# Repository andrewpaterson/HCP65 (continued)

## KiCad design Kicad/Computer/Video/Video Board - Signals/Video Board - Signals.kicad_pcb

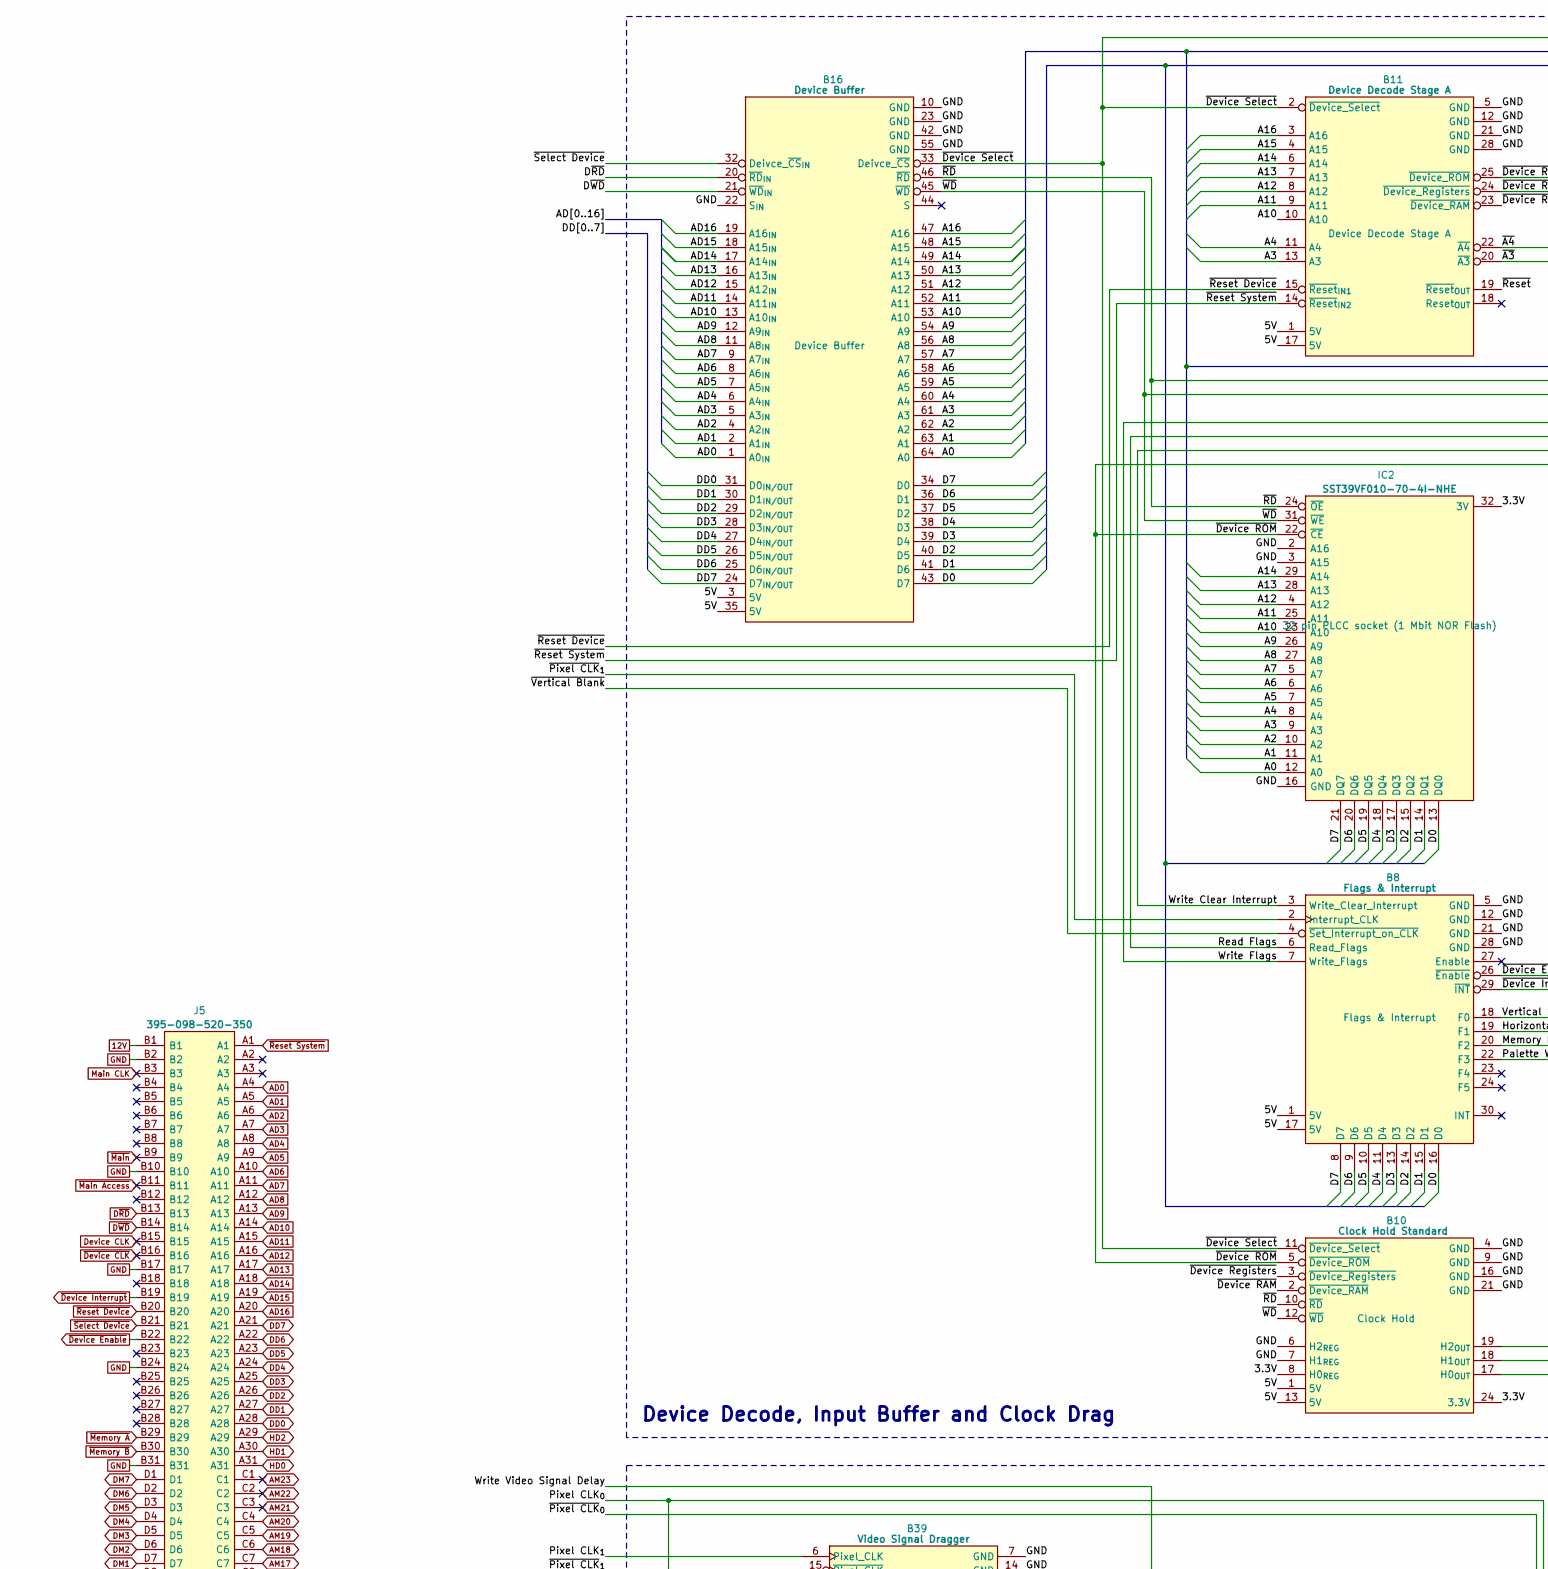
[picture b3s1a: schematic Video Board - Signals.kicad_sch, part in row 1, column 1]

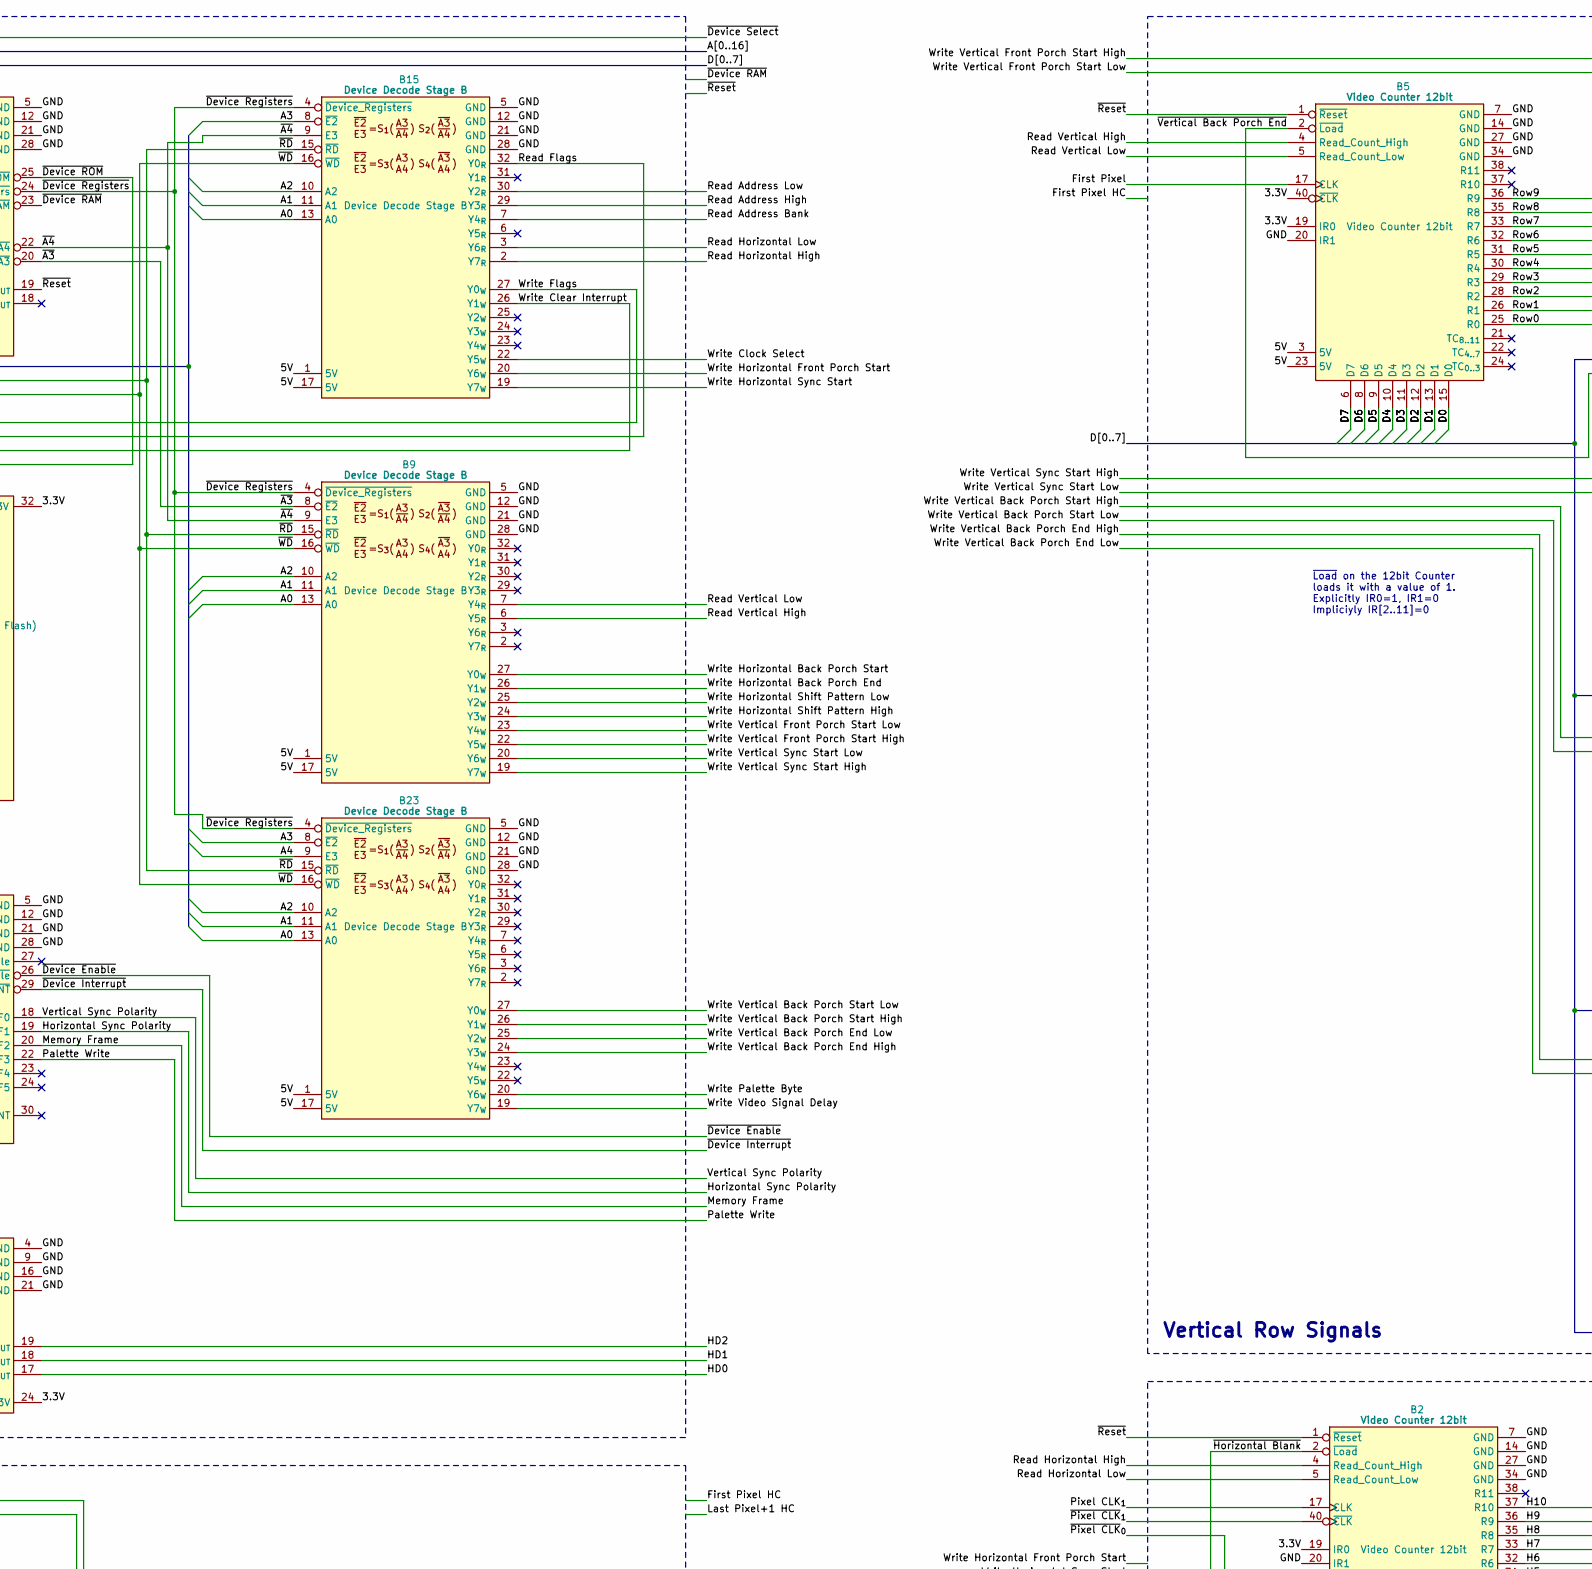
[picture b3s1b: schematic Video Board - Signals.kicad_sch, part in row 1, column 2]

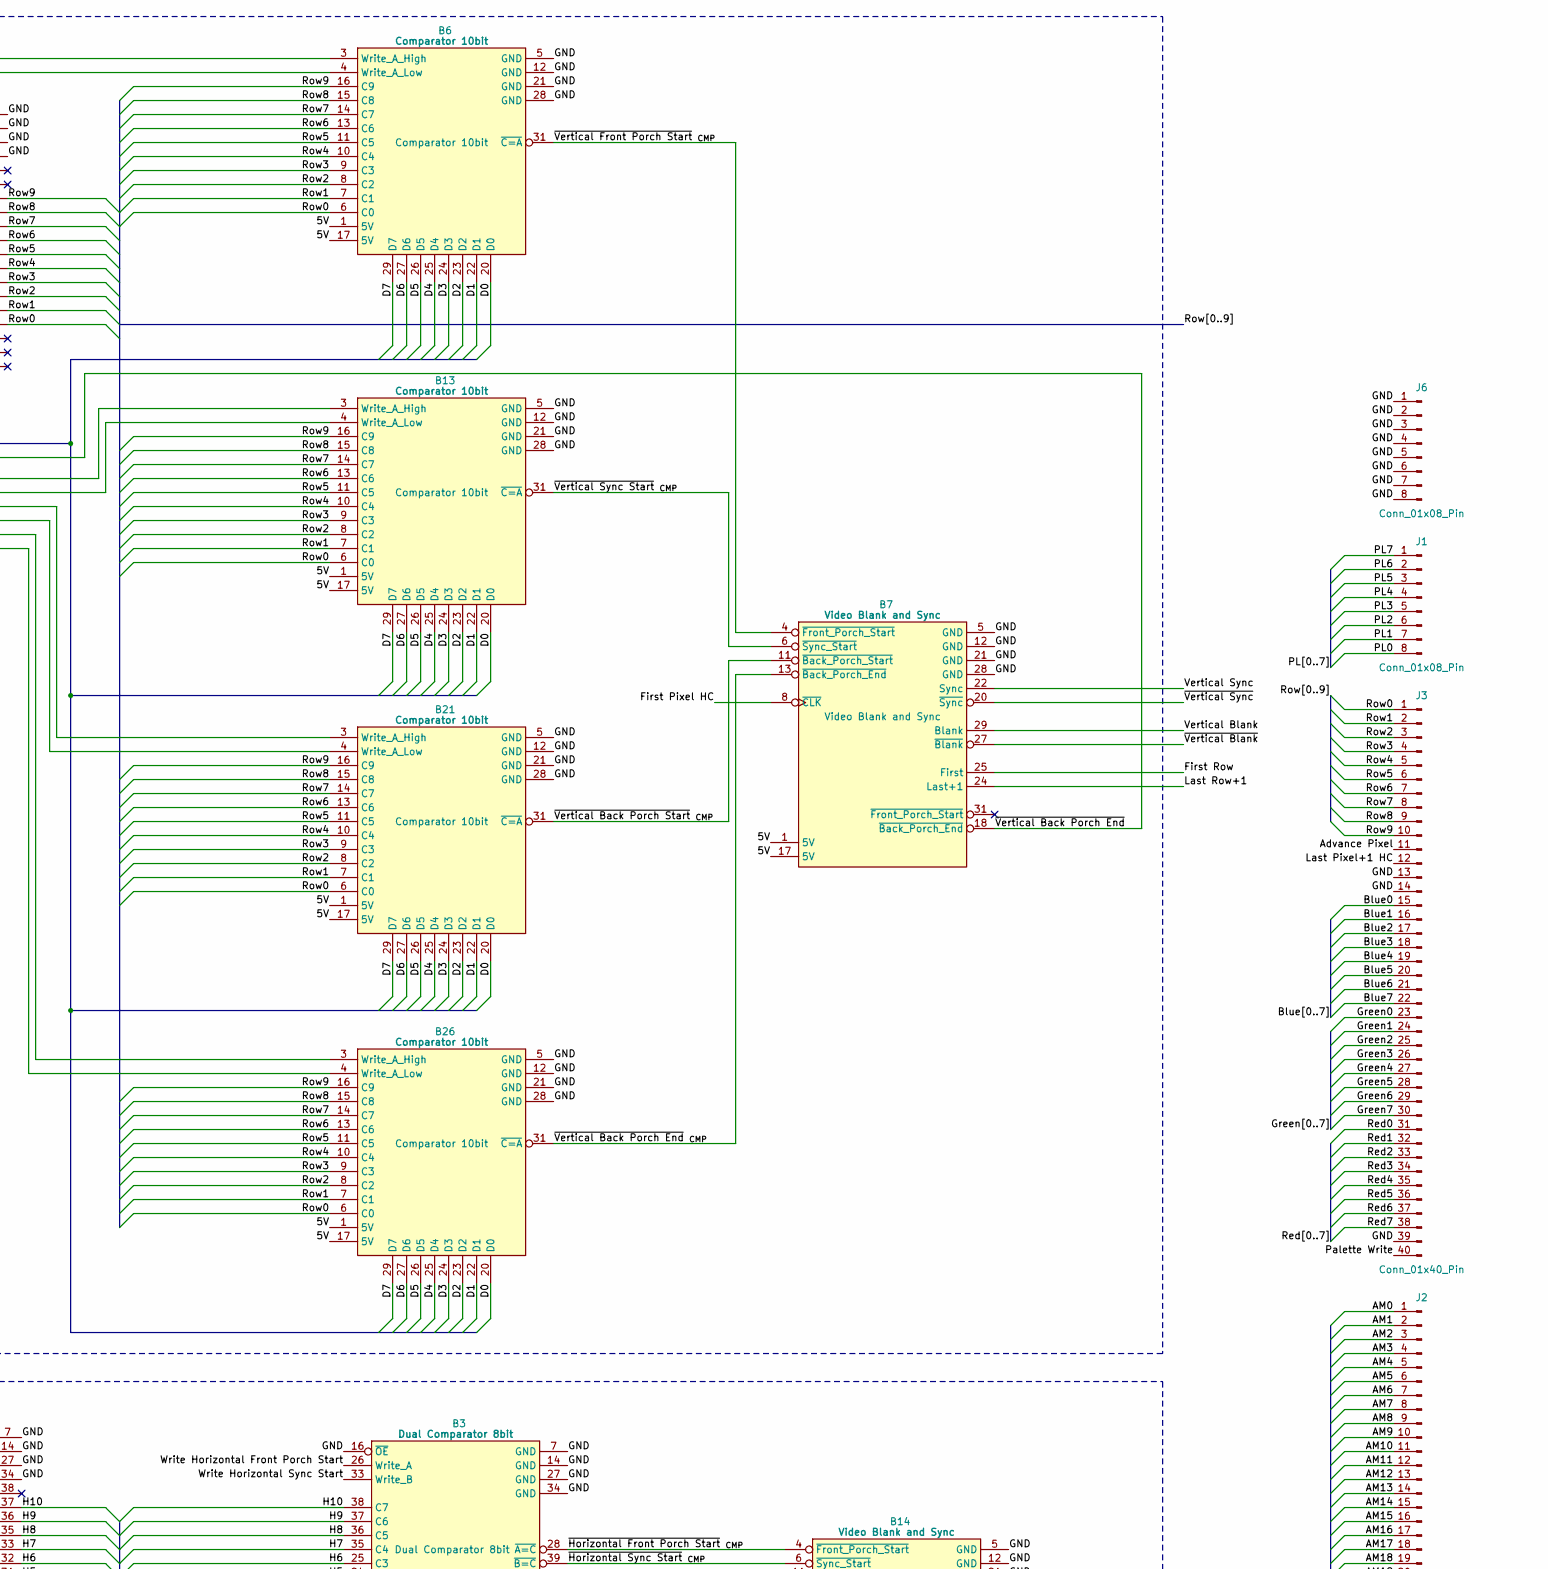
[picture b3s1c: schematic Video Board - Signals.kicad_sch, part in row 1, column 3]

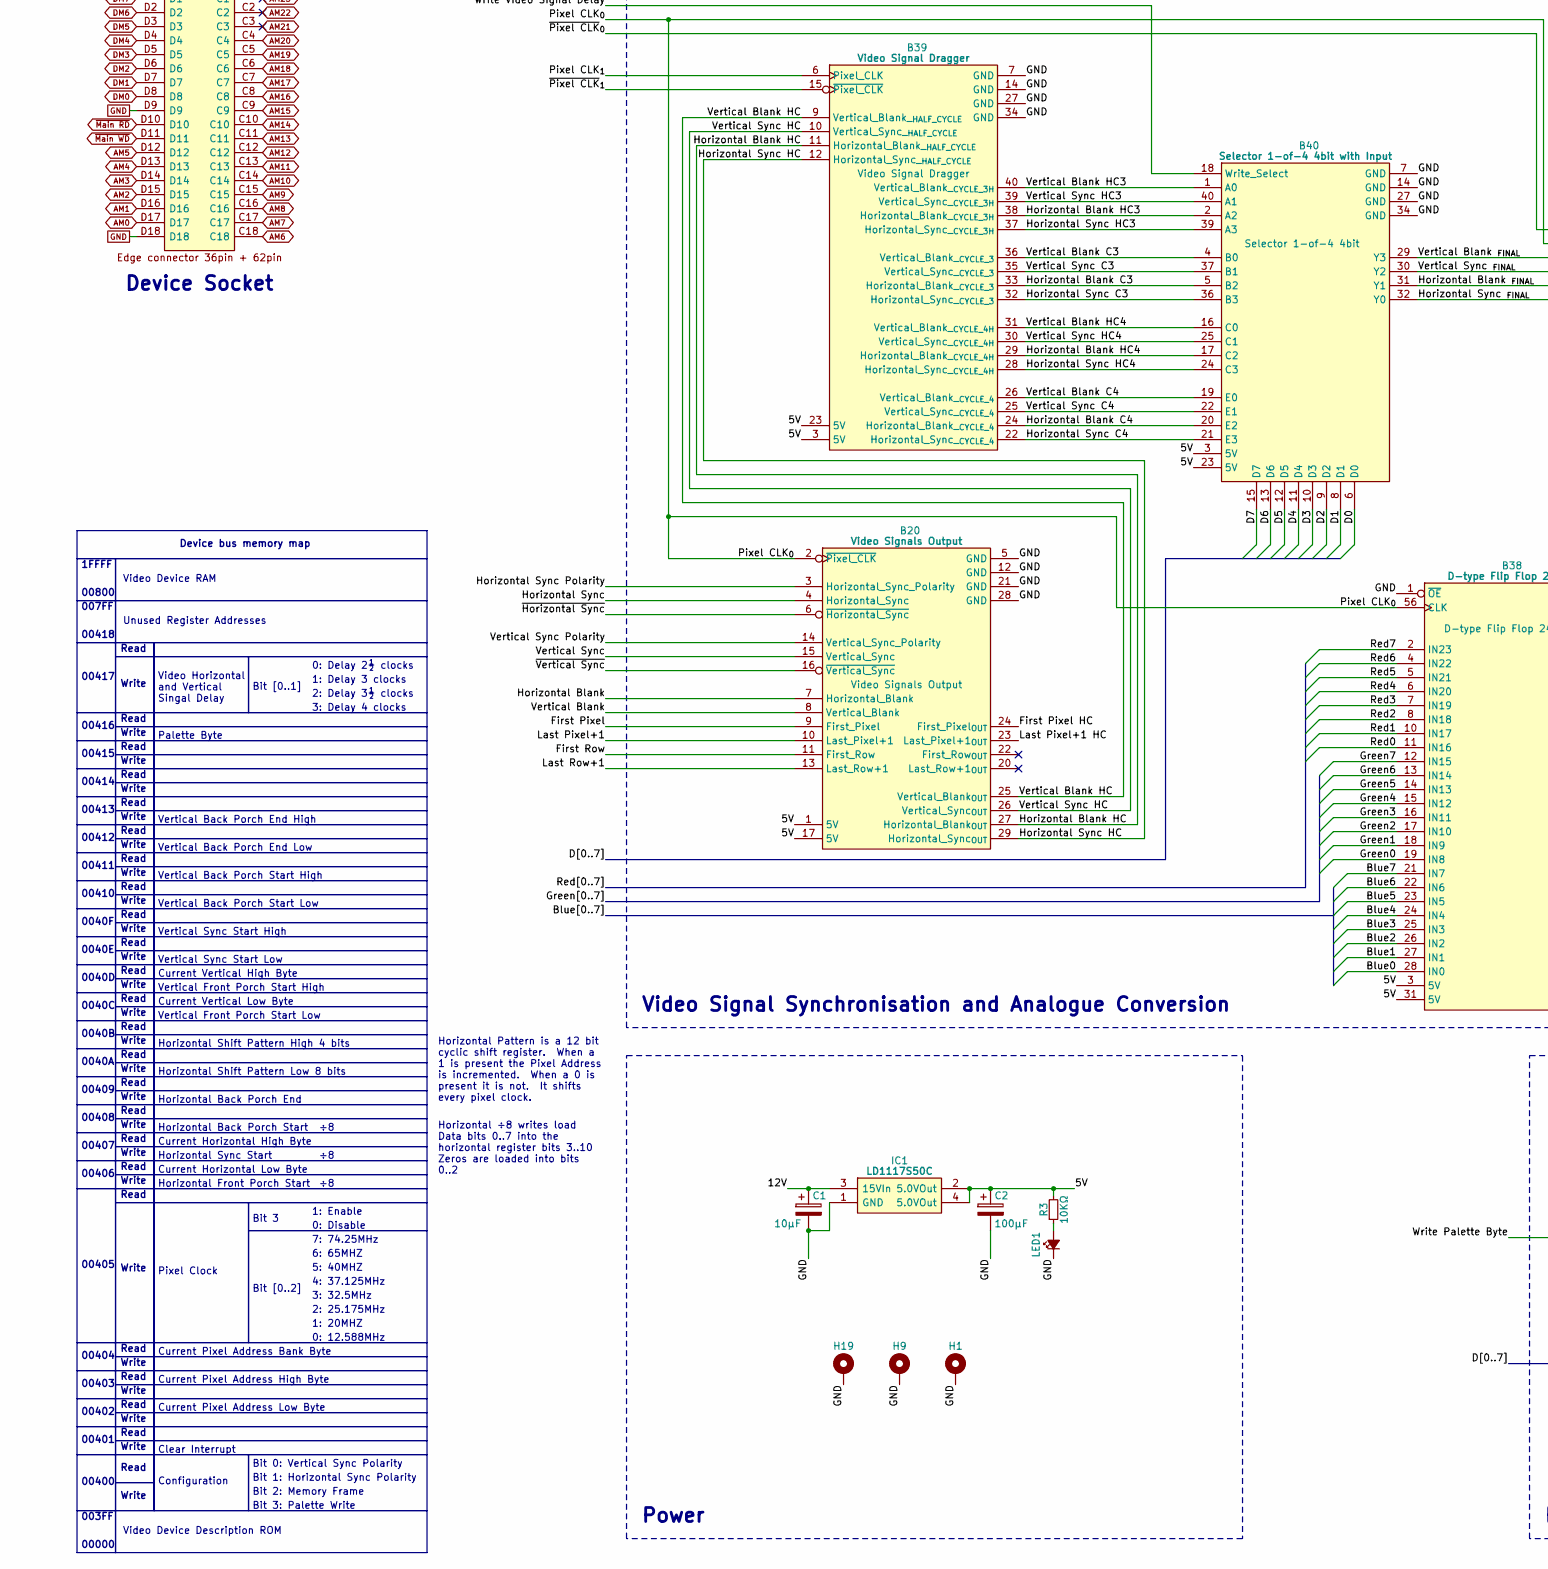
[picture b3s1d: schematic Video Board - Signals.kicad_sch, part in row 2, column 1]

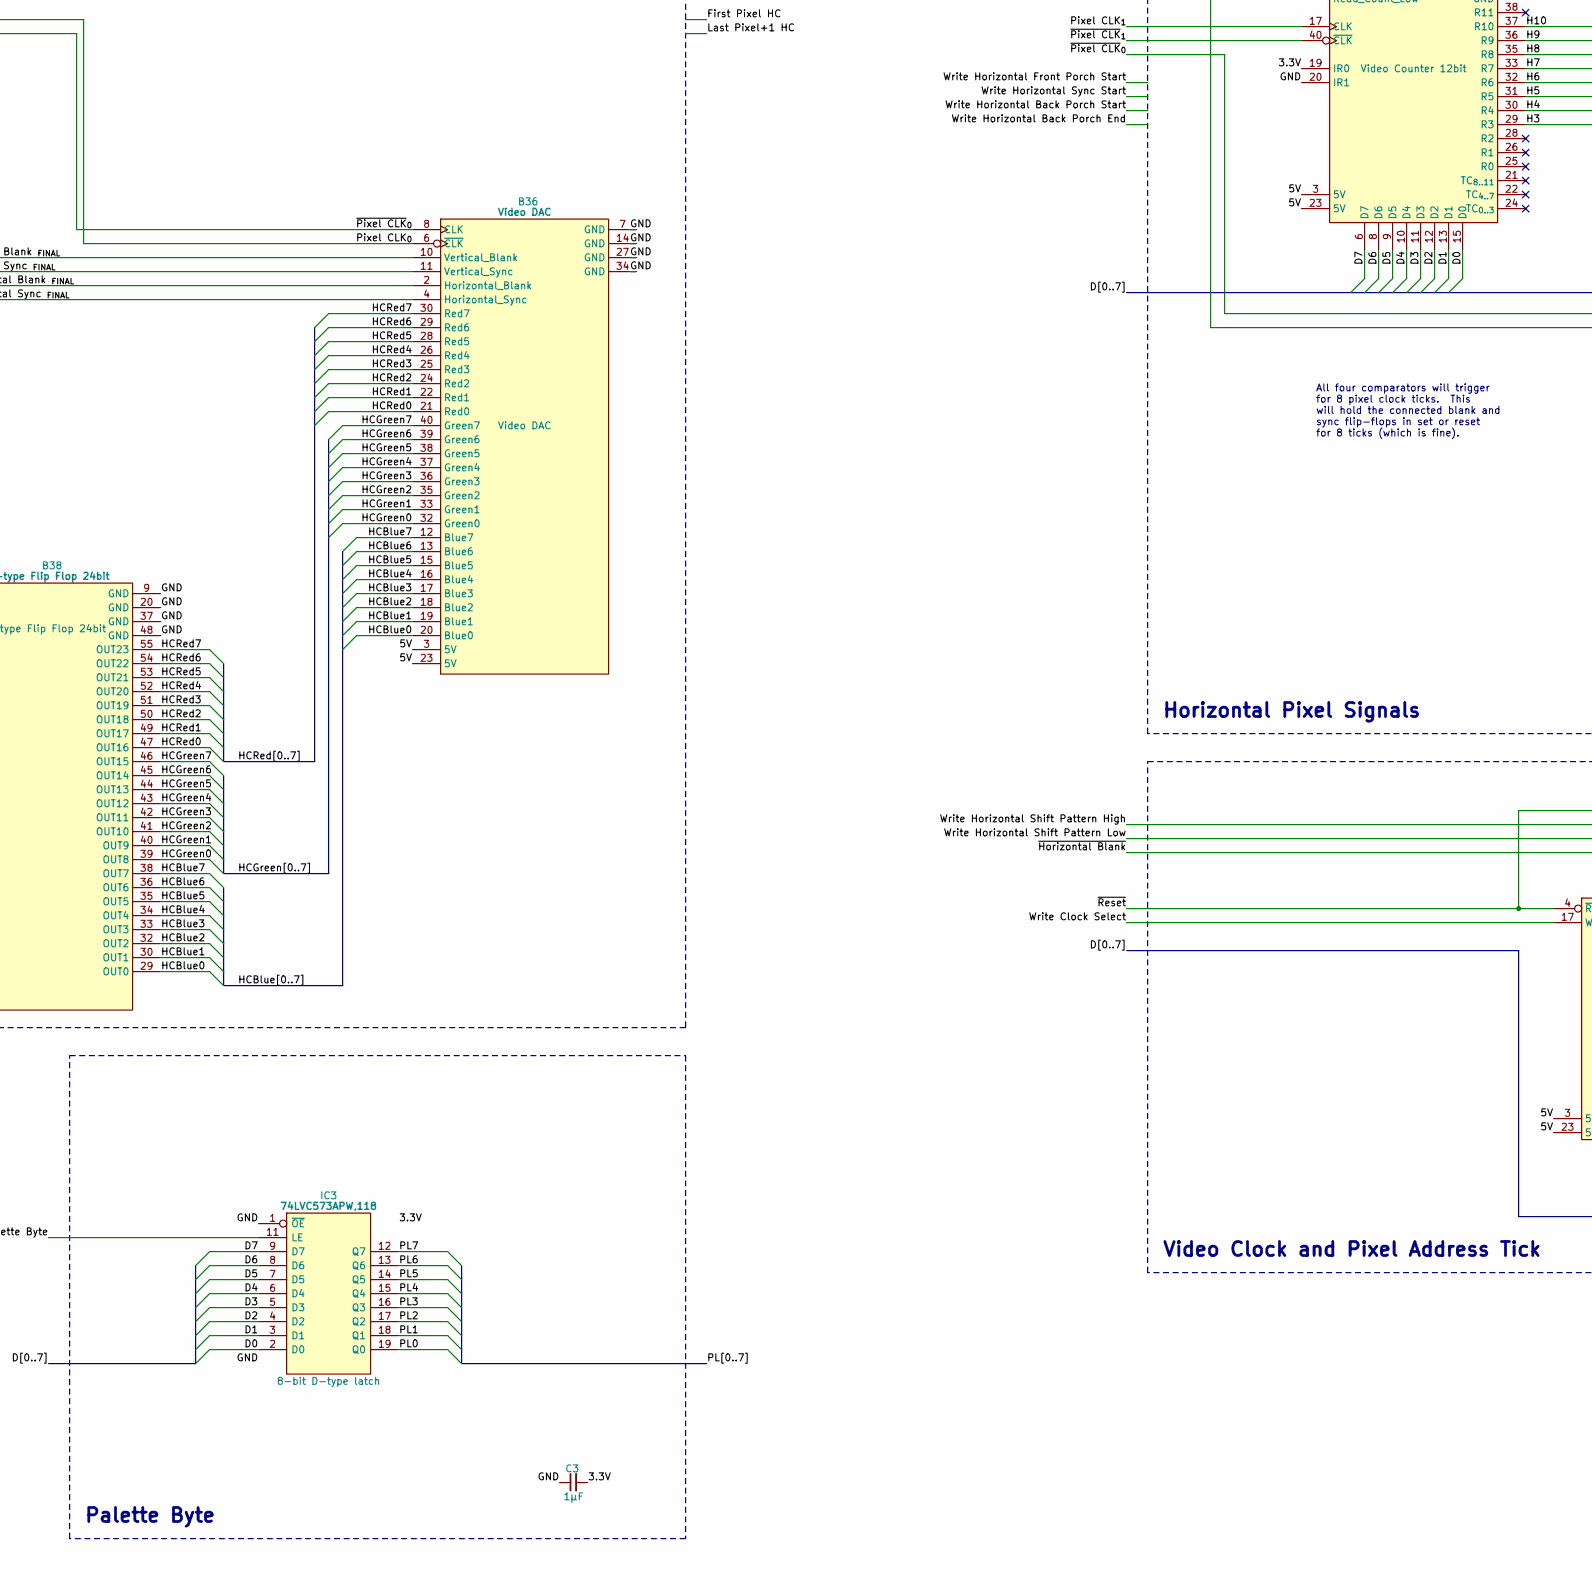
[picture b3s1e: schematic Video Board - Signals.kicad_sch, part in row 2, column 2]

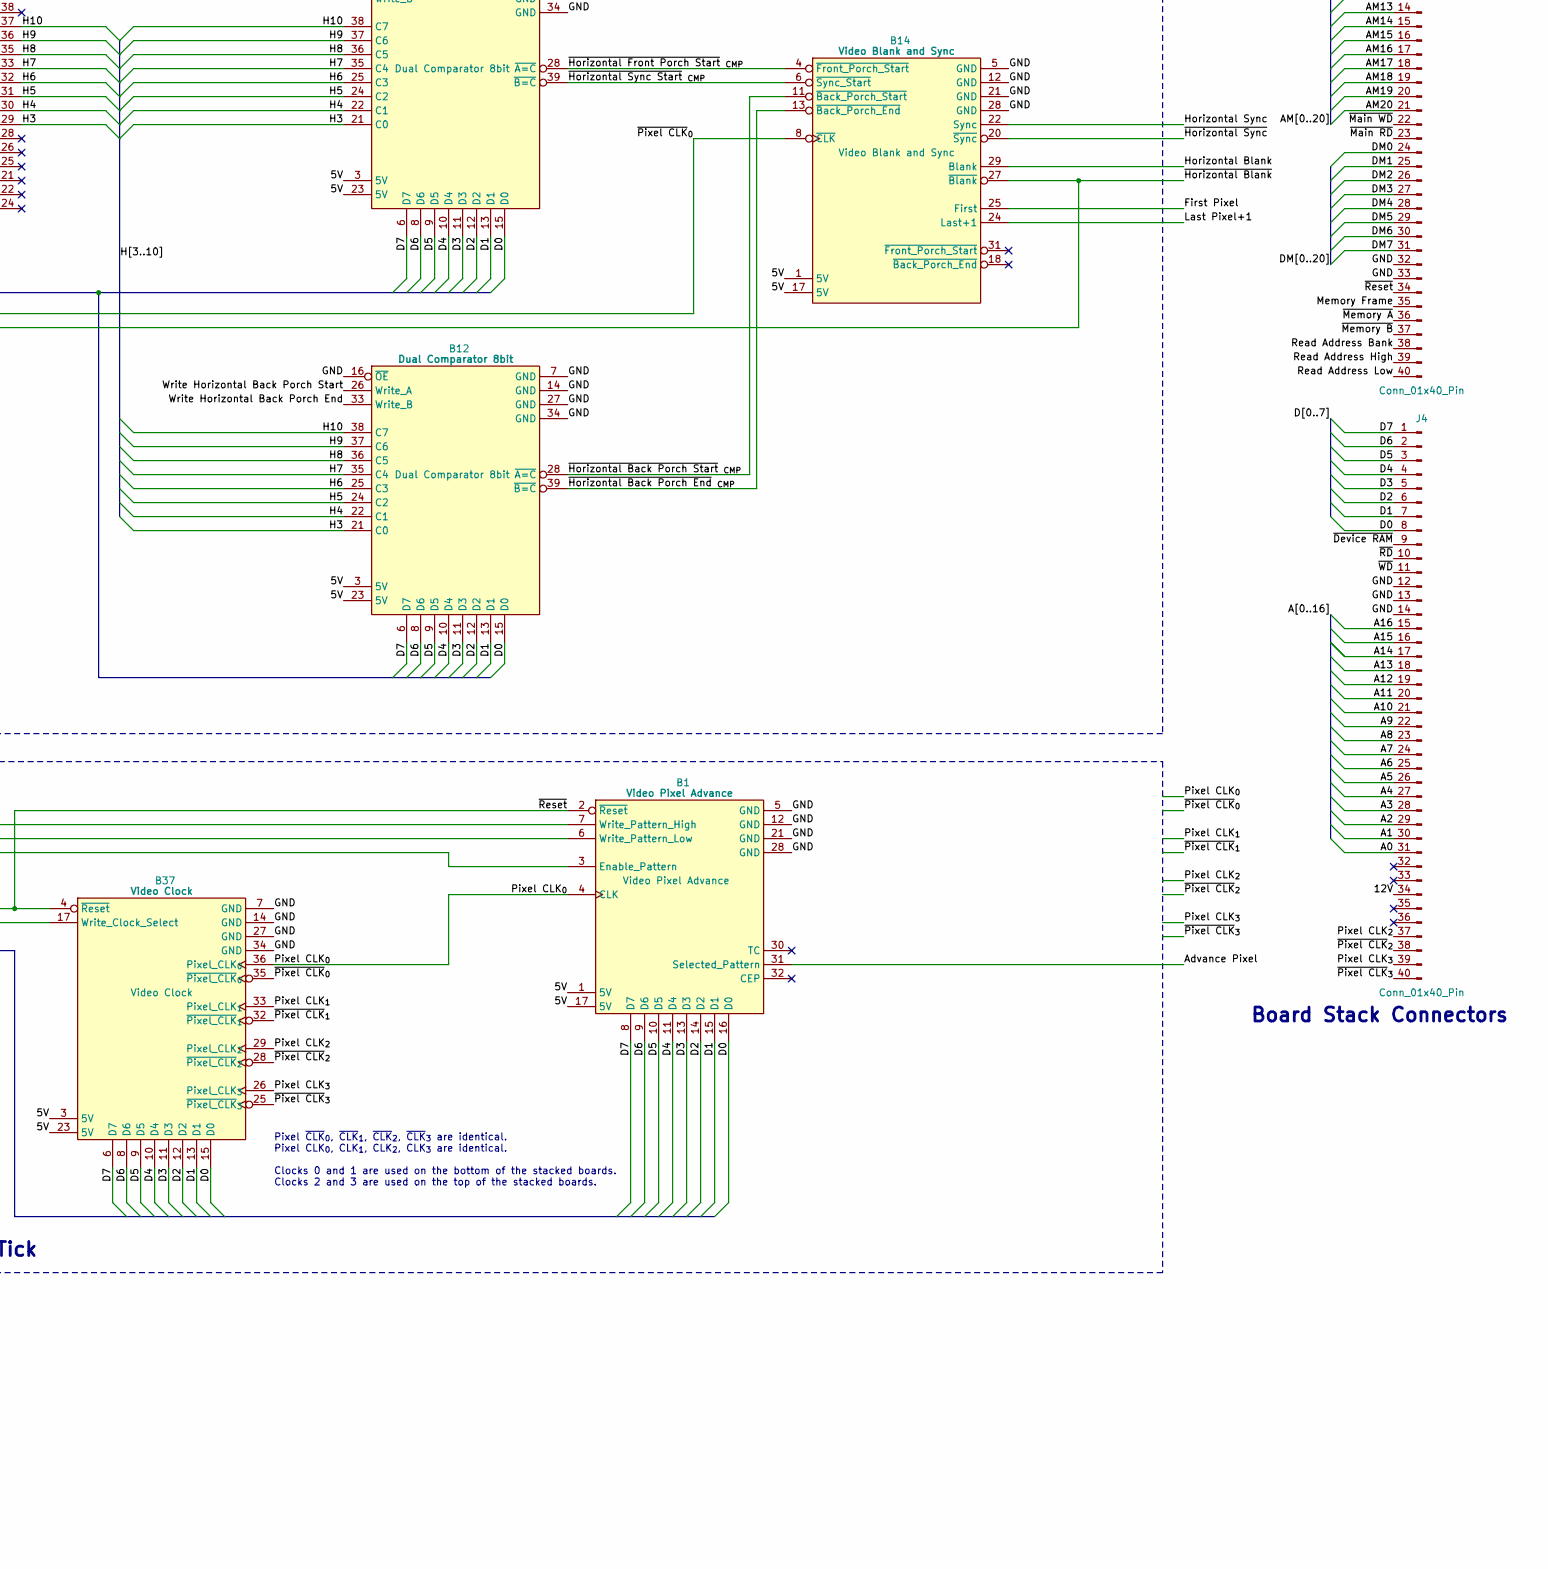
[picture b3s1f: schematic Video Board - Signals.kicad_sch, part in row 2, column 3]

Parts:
B1: Video Pixel Advance; HCP65_Video_Pixel_Advance
B2, B5: Video Counter 12bit; HCP65_Video_Counter_12bit
B3, B12: Dual Comparator 8bit; HCP65_Dual_Comparator_8bit
B6, B13, B21, B26: Comparator 10bit; HCP65_Comparator_10bit
B7, B14: Video Blank and Sync; HCP65_Video_Blank_and_Sync
B8: Flags & Interrupt; HCP65_Flags_Interrupt
B9, B15, B23: Device Decode Stage B; HCP65_Device_Decode_Stage_B
B10: Clock Hold Standard; HCP65_Clock_Hold_Standard
B11: Device Decode Stage A; HCP65_Device_Decode_Stage_A
B16: Device Buffer; HCP65_Device_Buffer
B20: Video Signals Output; HCP65_Video_Output_Signals
B36: Video DAC; HCP65_Video_DAC
B37: Video Clock; HCP65_Video_Clock
B38: D-type Flip Flop 24bit; HCP65_D_Flip_Flop_24bit
B39: Video Signal Dragger; HCP65_Video_Signal_Dragger
B40: Selector 1-of-4 4bit with Input; HCP65_Selector_1_of_4_4bit_with_Input
C1: 10μF; CP_Radial_D4.0mm_P2.00mm
C2: 100μF; CP_Radial_D4.0mm_P2.00mm
C3: 1μF; C_0805
H1, H9, H19: MountingHole_Pad; HCP65_MountingHole_M3_
IC1: LD1117S50C; LD1117S33C; Manufacturer_Part_Number LD1117S50C
IC2: SST39VF010-70-4I-NHE; 5408803224008; Manufacturer_Part_Number SST39VF010-70-4I-NHE
IC3: 74LVC573APW,118; SOP65P640X110-20N; Mouser Part Number 771-74LVC573APW-T
J1, J6: Conn_01x08_Pin; PinHeader_2x04_P2.54mm_Vertical
J2, J3, J4: Conn_01x40_Pin; PinHeader_2x20_P2.54mm_Vertical
J5: 395-098-520-350; 98pin Edge Connector; Manufacturer_Part_Number 395-098-520-350; Mouser Part Number 587-395-098-520-350
LED1: LED; LED_D5.0mm
R3: 10KΩ; R_0805

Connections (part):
12V: C1.1, IC1.3 (15VIn), J4.34, J5.B1
/3.3V: B2.19 (IR0), B5.19 (IR0), B5.40 (~CLK), B10.8 (H0_{REG}), B10.24 (3.3V), C3.2, IC2.32 (3V), IC3.20 (3V)
/5V: B1.1 (5V), B1.17 (5V), B2.3 (5V), B2.23 (5V), B3.3 (5V), B3.23 (5V), B5.3 (5V), B5.23 (5V), B6.1 (5V), B6.17 (5V), B7.1 (5V), B7.17 (5V), B8.1 (5V), B8.17 (5V), B9.1 (5V), B9.17 (5V), B10.1 (5V), B10.13 (5V), B11.1 (5V), B11.17 (5V), B12.3 (5V), B12.23 (5V), B13.1 (5V), B13.17 (5V), B14.1 (5V), B14.17 (5V), B15.1 (5V), B15.17 (5V), B16.3 (5V), B16.35 (5V), B20.1 (5V), B20.17 (5V), B21.1 (5V), B21.17 (5V), B23.1 (5V), B23.17 (5V), B26.1 (5V), B26.17 (5V), B36.3 (5V), B36.23 (5V), B37.3 (5V), B37.23 (5V), B38.3 (5V), B38.31 (5V), B39.3 (5V), B39.23 (5V), B40.3 (5V), B40.23 (5V), C2.1, IC1.2 (5.0VOut), IC1.4 (5.0VOut), R3.2
/A0: B9.13 (A0), B15.13 (A0), B16.64 (A0), B23.13 (A0), IC2.12 (A0), J4.31
/A1: B9.11 (A1), B15.11 (A1), B16.63 (A1), B23.11 (A1), IC2.11 (A1), J4.30
/A2: B9.10 (A2), B15.10 (A2), B16.62 (A2), B23.10 (A2), IC2.10 (A2), J4.29
/A3: B11.13 (A3), B15.8 (~E2), B16.61 (A3), B23.8 (~E2), IC2.9 (A3), J4.28
/A4: B11.11 (A4), B16.60 (A4), B23.9 (E3), IC2.8 (A4), J4.27
/A5: B16.59 (A5), IC2.7 (A5), J4.26
/A6: B16.58 (A6), IC2.6 (A6), J4.25
/A7: B16.57 (A7), IC2.5 (A7), J4.24
/A8: B16.56 (A8), IC2.27 (A8), J4.23
/A9: B16.54 (A9), IC2.26 (A9), J4.22
/A10: B11.10 (A10), B16.53 (A10), IC2.23 (A10), J4.21
/A11: B11.9 (A11), B16.52 (A11), IC2.25 (A11), J4.20
/A12: B11.8 (A12), B16.51 (A12), IC2.4 (A12), J4.19
/A13: B11.7 (A13), B16.50 (A13), IC2.28 (A13), J4.18
/A14: B11.6 (A14), B16.49 (A14), IC2.29 (A14), J4.17
/A15: B11.4 (A15), B16.48 (A15), J4.16
/A16: B11.3 (A16), B16.47 (A16), J4.15
/Advance Pixel: B1.31 (Selected_Pattern), J3.11
/Blue0: B38.28 (IN0), J3.15
/Blue1: B38.27 (IN1), J3.16
/Blue2: B38.26 (IN2), J3.17
/Blue3: B38.25 (IN3), J3.18
/Blue4: B38.24 (IN4), J3.19
/Blue5: B38.23 (IN5), J3.20
/Blue6: B38.22 (IN6), J3.21
/Blue7: B38.21 (IN7), J3.22
/D0: B1.16 (D0), B2.15 (D0), B3.15 (D0), B5.15 (D0), B6.20 (D0), B8.16 (D0), B12.15 (D0), B13.20 (D0), B16.43 (D7), B21.20 (D0), B26.20 (D0), B37.15 (D0), B40.6 (D0), IC2.13 (DQ0), IC3.2 (D0), J4.8
/D1: B1.15 (D1), B2.13 (D1), B3.13 (D1), B5.13 (D1), B6.22 (D1), B8.15 (D1), B12.13 (D1), B13.22 (D1), B16.41 (D6), B21.22 (D1), B26.22 (D1), B37.13 (D1), B40.8 (D1), IC2.14 (DQ1), IC3.3 (D1), J4.7
/D2: B1.14 (D2), B2.12 (D2), B3.12 (D2), B5.12 (D2), B6.23 (D2), B8.14 (D2), B12.12 (D2), B13.23 (D2), B16.40 (D5), B21.23 (D2), B26.23 (D2), B37.12 (D2), B40.9 (D2), IC2.15 (DQ2), IC3.4 (D2), J4.6
/D3: B1.13 (D3), B2.11 (D3), B3.11 (D3), B5.11 (D3), B6.24 (D3), B8.13 (D3), B12.11 (D3), B13.24 (D3), B16.39 (D4), B21.24 (D3), B26.24 (D3), B37.11 (D3), B40.10 (D3), IC2.17 (DQ3), IC3.5 (D3), J4.5
/D4: B1.11 (D4), B2.10 (D4), B3.10 (D4), B5.10 (D4), B6.25 (D4), B8.11 (D4), B12.10 (D4), B13.25 (D4), B16.38 (D3), B21.25 (D4), B26.25 (D4), B37.10 (D4), B40.11 (D4), IC2.18 (DQ4), IC3.6 (D4), J4.4
/D5: B1.10 (D5), B2.9 (D5), B3.9 (D5), B5.9 (D5), B6.26 (D5), B8.10 (D5), B12.9 (D5), B13.26 (D5), B16.37 (D2), B21.26 (D5), B26.26 (D5), B37.9 (D5), B40.12 (D5), IC2.19 (DQ5), IC3.7 (D5), J4.3
/D6: B1.9 (D6), B2.8 (D6), B3.8 (D6), B5.8 (D6), B6.27 (D6), B8.9 (D6), B12.8 (D6), B13.27 (D6), B16.36 (D1), B21.27 (D6), B26.27 (D6), B37.8 (D6), B40.13 (D6), IC2.20 (DQ6), IC3.8 (D6), J4.2
/D7: B1.8 (D7), B2.6 (D7), B3.6 (D7), B5.6 (D7), B6.29 (D7), B8.8 (D7), B12.6 (D7), B13.29 (D7), B16.34 (D0), B21.29 (D7), B26.29 (D7), B37.6 (D7), B40.15 (D7), IC2.21 (DQ7), IC3.9 (D7), J4.1
/First Pixel: B5.17 (CLK), B14.25 (First), B20.9 (First_Pixel)
/First Pixel HC: B7.8 (~CLK), B20.24 (First_Pixel_{OUT})
/First Row: B7.25 (First), B20.11 (First_Row)
/Green0: B38.19 (IN8), J3.23
/Green1: B38.18 (IN9), J3.24
/Green2: B38.17 (IN10), J3.25
/Green3: B38.16 (IN11), J3.26
/Green4: B38.15 (IN12), J3.27
/Green5: B38.14 (IN13), J3.28
/Green6: B38.13 (IN14), J3.29
/Green7: B38.12 (IN15), J3.30
/H3: B2.29 (R3), B3.21 (C0), B12.21 (C0)
/H4: B2.30 (R4), B3.22 (C1), B12.22 (C1)
/H5: B2.31 (R5), B3.24 (C2), B12.24 (C2)
/H6: B2.32 (R6), B3.25 (C3), B12.25 (C3)
/H7: B2.33 (R7), B3.35 (C4), B12.35 (C4)
/H8: B2.35 (R8), B3.36 (C5), B12.36 (C5)
/H9: B2.36 (R9), B3.37 (C6), B12.37 (C6)
/H10: B2.37 (R10), B3.38 (C7), B12.38 (C7)
/HCBlue0: B36.20 (Blue0), B38.29 (OUT0)
/HCBlue1: B36.19 (Blue1), B38.30 (OUT1)
/HCBlue2: B36.18 (Blue2), B38.32 (OUT2)
/HCBlue3: B36.17 (Blue3), B38.33 (OUT3)
/HCBlue4: B36.16 (Blue4), B38.34 (OUT4)
/HCBlue5: B36.15 (Blue5), B38.35 (OUT5)
/HCBlue6: B36.13 (Blue6), B38.36 (OUT6)
/HCBlue7: B36.12 (Blue7), B38.38 (OUT7)
/HCGreen0: B36.32 (Green0), B38.39 (OUT8)
/HCGreen1: B36.33 (Green1), B38.40 (OUT9)
/HCGreen2: B36.35 (Green2), B38.41 (OUT10)
/HCGreen3: B36.36 (Green3), B38.42 (OUT11)
/HCGreen4: B36.37 (Green4), B38.43 (OUT12)
/HCGreen5: B36.38 (Green5), B38.44 (OUT13)
/HCGreen6: B36.39 (Green6), B38.45 (OUT14)
/HCGreen7: B36.40 (Green7), B38.46 (OUT15)
/HCRed0: B36.21 (Red0), B38.47 (OUT16)
/HCRed1: B36.22 (Red1), B38.49 (OUT17)
/HCRed2: B36.24 (Red2), B38.50 (OUT18)
/HCRed3: B36.25 (Red3), B38.51 (OUT19)
/HCRed4: B36.26 (Red4), B38.52 (OUT20)
/HCRed5: B36.28 (Red5), B38.53 (OUT21)
/HCRed6: B36.29 (Red6), B38.54 (OUT22)
/HCRed7: B36.30 (Red7), B38.55 (OUT23)
/Horizontal Blank: B14.29 (Blank), B20.7 (Horizontal_Blank)
/Horizontal Blank C3: B39.33 (Horizontal_Blank__{CYCLE_3}), B40.5 (B2)
/Horizontal Blank C4: B39.24 (Horizontal_Blank__{CYCLE_4}), B40.20 (E2)
/Horizontal Blank HC: B20.27 (Horizontal_Blank_{OUT}), B39.11 (Horizontal_Blank__{HALF_CYCLE})
/Horizontal Blank HC3: B39.38 (Horizontal_Blank__{CYCLE_3H}), B40.2 (A2)
/Horizontal Blank HC4: B39.29 (Horizontal_Blank__{CYCLE_4H}), B40.17 (C2)
/Horizontal Blank _{FINAL}: B36.2 (Horizontal_Blank), B40.31 (Y1)
/Horizontal Sync: B14.22 (Sync), B20.4 (Horizontal_Sync)
/Horizontal Sync C3: B39.32 (Horizontal_Sync__{CYCLE_3}), B40.36 (B3)
/Horizontal Sync C4: B39.22 (Horizontal_Sync__{CYCLE_4}), B40.21 (E3)
/Horizontal Sync HC: B20.29 (Horizontal_Sync_{OUT}), B39.12 (Horizontal_Sync__{HALF_CYCLE})
/Horizontal Sync HC3: B39.37 (Horizontal_Sync__{CYCLE_3H}), B40.39 (A3)
/Horizontal Sync HC4: B39.28 (Horizontal_Sync__{CYCLE_4H}), B40.24 (C3)
/Horizontal Sync Polarity: B8.19 (F1), B20.3 (Horizontal_Sync_Polarity)
/Horizontal Sync _{FINAL}: B36.4 (Horizontal_Sync), B40.32 (Y0)
/Last Pixel+1: B14.24 (Last+1), B20.10 (Last_Pixel+1)
/Last Pixel+1 HC: B20.23 (Last_Pixel+1_{OUT}), J3.12
/Last Row+1: B7.24 (Last+1), B20.13 (Last_Row+1)
/Memory Frame: B8.20 (F2), J2.35
/PL0: IC3.19 (Q0), J1.8
/PL1: IC3.18 (Q1), J1.7
/PL2: IC3.17 (Q2), J1.6
/PL3: IC3.16 (Q3), J1.5
/PL4: IC3.15 (Q4), J1.4
/PL5: IC3.14 (Q5), J1.3
/PL6: IC3.13 (Q6), J1.2
/PL7: IC3.12 (Q7), J1.1
/Palette Write: B8.22 (F3), J3.40
/Pixel CLK_{0}: B1.4 (CLK), B20.2 (~Pixel_CLK), B36.6 (~CLK), B37.36 (Pixel_CLK_{0}), B38.56 (CLK)
/Pixel CLK_{1}: B2.17 (CLK), B37.33 (Pixel_CLK_{1}), B39.6 (Pixel_CLK)
/Pixel CLK_{2}: B37.29 (Pixel_CLK_{2}), J4.37
/Pixel CLK_{3}: B37.26 (Pixel_CLK_{3}), J4.39
/Read Address Bank: B15.7 (Y4_{R}), J2.38
/Read Address High: B15.29 (Y3_{R}), J2.39
/Read Address Low: B15.30 (Y2_{R}), J2.40
/Read Flags: B8.6 (Read_Flags), B15.32 (Y0_{R})
/Read Horizontal High: B2.4 (Read_Count_High), B15.2 (Y7_{R})
/Read Horizontal Low: B2.5 (Read_Count_Low), B15.3 (Y6_{R})
/Read Vertical High: B5.4 (Read_Count_High), B9.6 (Y5_{R})
/Read Vertical Low: B5.5 (Read_Count_Low), B9.7 (Y4_{R})
/Red0: B38.11 (IN16), J3.31
/Red1: B38.10 (IN17), J3.32
/Red2: B38.8 (IN18), J3.33
/Red3: B38.7 (IN19), J3.34
/Red4: B38.6 (IN20), J3.35
/Red5: B38.5 (IN21), J3.36
/Red6: B38.4 (IN22), J3.37
/Red7: B38.2 (IN23), J3.38
/Row0: B5.25 (R0), B6.6 (C0), B13.6 (C0), B21.6 (C0), B26.6 (C0), J3.1
/Row1: B5.26 (R1), B6.7 (C1), B13.7 (C1), B21.7 (C1), B26.7 (C1), J3.2
/Row2: B5.28 (R2), B6.8 (C2), B13.8 (C2), B21.8 (C2), B26.8 (C2), J3.3
/Row3: B5.29 (R3), B6.9 (C3), B13.9 (C3), B21.9 (C3), B26.9 (C3), J3.4
/Row4: B5.30 (R4), B6.10 (C4), B13.10 (C4), B21.10 (C4), B26.10 (C4), J3.5
/Row5: B5.31 (R5), B6.11 (C5), B13.11 (C5), B21.11 (C5), B26.11 (C5), J3.6
/Row6: B5.32 (R6), B6.13 (C6), B13.13 (C6), B21.13 (C6), B26.13 (C6), J3.7
/Row7: B5.33 (R7), B6.14 (C7), B13.14 (C7), B21.14 (C7), B26.14 (C7), J3.8
/Row8: B5.35 (R8), B6.15 (C8), B13.15 (C8), B21.15 (C8), B26.15 (C8), J3.9
/Row9: B5.36 (R9), B6.16 (C9), B13.16 (C9), B21.16 (C9), B26.16 (C9), J3.10
/Vertical Blank: B7.29 (Blank), B20.8 (Vertical_Blank)
/Vertical Blank C3: B39.36 (Vertical_Blank__{CYCLE_3}), B40.4 (B0)
/Vertical Blank C4: B39.26 (Vertical_Blank__{CYCLE_4}), B40.19 (E0)
/Vertical Blank HC: B20.25 (Vertical_Blank_{OUT}), B39.9 (Vertical_Blank__{HALF_CYCLE})
/Vertical Blank HC3: B39.40 (Vertical_Blank__{CYCLE_3H}), B40.1 (A0)
/Vertical Blank HC4: B39.31 (Vertical_Blank__{CYCLE_4H}), B40.16 (C0)
/Vertical Blank _{FINAL}: B36.10 (Vertical_Blank), B40.29 (Y3)
/Vertical Sync: B7.22 (Sync), B20.15 (Vertical_Sync)
/Vertical Sync C3: B39.35 (Vertical_Sync__{CYCLE_3}), B40.37 (B1)
/Vertical Sync C4: B39.25 (Vertical_Sync__{CYCLE_4}), B40.22 (E1)
/Vertical Sync HC: B20.26 (Vertical_Sync_{OUT}), B39.10 (Vertical_Sync__{HALF_CYCLE})
/Vertical Sync HC3: B39.39 (Vertical_Sync__{CYCLE_3H}), B40.40 (A1)
/Vertical Sync HC4: B39.30 (Vertical_Sync__{CYCLE_4H}), B40.25 (C1)
/Vertical Sync Polarity: B8.18 (F0), B20.14 (Vertical_Sync_Polarity)
/Vertical Sync _{FINAL}: B36.11 (Vertical_Sync), B40.30 (Y2)
/Write Clear Interrupt: B8.3 (Write_Clear_Interrupt), B15.26 (Y1_{W})
/Write Clock Select: B15.22 (Y5_{W}), B37.17 (Write_Clock_Select)
/Write Flags: B8.7 (Write_Flags), B15.27 (Y0_{W})
/Write Horizontal Back Porch End: B9.26 (Y1_{W}), B12.33 (Write_B)
/Write Horizontal Back Porch Start: B9.27 (Y0_{W}), B12.26 (Write_A)
/Write Horizontal Front Porch Start: B3.26 (Write_A), B15.20 (Y6_{W})
/Write Horizontal Shift Pattern High: B1.7 (Write_Pattern_High), B9.24 (Y3_{W})
/Write Horizontal Shift Pattern Low: B1.6 (Write_Pattern_Low), B9.25 (Y2_{W})
/Write Horizontal Sync Start: B3.33 (Write_B), B15.19 (Y7_{W})
/Write Palette Byte: B23.20 (Y6_{W}), IC3.11 (LE)
/Write Vertical Back Porch End High: B23.24 (Y3_{W}), B26.3 (Write_A_High)
/Write Vertical Back Porch End Low: B23.25 (Y2_{W}), B26.4 (Write_A_Low)
/Write Vertical Back Porch Start High: B21.3 (Write_A_High), B23.26 (Y1_{W})
/Write Vertical Back Porch Start Low: B21.4 (Write_A_Low), B23.27 (Y0_{W})
/Write Vertical Front Porch Start High: B6.3 (Write_A_High), B9.22 (Y5_{W})
/Write Vertical Front Porch Start Low: B6.4 (Write_A_Low), B9.23 (Y4_{W})
/Write Vertical Sync Start High: B9.19 (Y7_{W}), B13.3 (Write_A_High)
/Write Vertical Sync Start Low: B9.20 (Y6_{W}), B13.4 (Write_A_Low)
/Write Video Signal Delay: B23.19 (Y7_{W}), B40.18 (Write_Select)
/~A3: B9.8 (~E2), B11.20 (~A3)
/~A4: B9.9 (E3), B11.22 (~A4), B15.9 (E3)
/~Device RAM: B10.2 (~Device_RAM), B11.23 (~Device_RAM), J4.9
/~Device ROM: B10.5 (~Device_ROM), B11.25 (~Device_ROM), IC2.22 (~CE)
/~Device Registers: B9.4 (~Device_Registers), B10.3 (~Device_Registers), B11.24 (~Device_Registers), B15.4 (~Device_Registers), B23.4 (~Device_Registers)
/~Device Select: B10.11 (~Device_Select), B11.2 (~Device_Select), B16.33 (Deivce_~CS)
/~Horizontal Back Porch End _{CMP}: B12.39 (~B=C), B14.13 (~Back_Porch_End)
/~Horizontal Back Porch Start _{CMP}: B12.28 (~A=C), B14.11 (~Back_Porch_Start)
/~Horizontal Blank: B1.3 (Enable_Pattern), B2.2 (~Load), B14.27 (~Blank)
/~Horizontal Front Porch Start _{CMP}: B3.28 (~A=C), B14.4 (~Front_Porch_Start)
/~Horizontal Sync Start _{CMP}: B3.39 (~B=C), B14.6 (~Sync_Start)
/~Horizontal Sync: B14.20 (~Sync), B20.6 (~Horizontal_Sync)
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
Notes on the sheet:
Bit [0..2]
Video Device Description ROM
Write
00404
007FF
00414
00411
Read
Horizontal Back Porch End
Pixel Clock
00400
Horizontal Pixel Signals
00401
Horizontal Pattern is a 12 bit cyclic shift register. When a 1 is present the Pixel Address is incremented. When a 0 is present it is not. It shifts every pixel clock.
0040A
Current Horizontal Low Byte
0040E
Device Socket
Configuration
1: Delay 3 clocks
00406
Video Clock and Pixel Address Tick
0: Delay 2½ clocks
3: Delay 4 clocks
Vertical Front Porch Start High
3: 32.5MHz
Video Horizontal and Vertical Singal Delay
Current Pixel Address Low Byte
Vertical Row Signals
Horizontal Sync Start
Current Pixel Address High Byte
00413
2: Delay 3½ clocks
Pixel ~{CLK}_{0}, ~{CLK}_{1}, ~{CLK}_{2}, ~{CLK}_{3} are identical. Pixel CLK_{0}, CLK_{1}, CLK_{2}, CLK_{3} are identical. Clocks 0 and 1 are used on the bottom of the stacked boards. Clocks 2 and 3 are used on the top of the stacked boards.
Vertical Sync Start High
00407
1: Enable
Vertical Sync Start Low
1FFFF
Current Vertical Low Byte

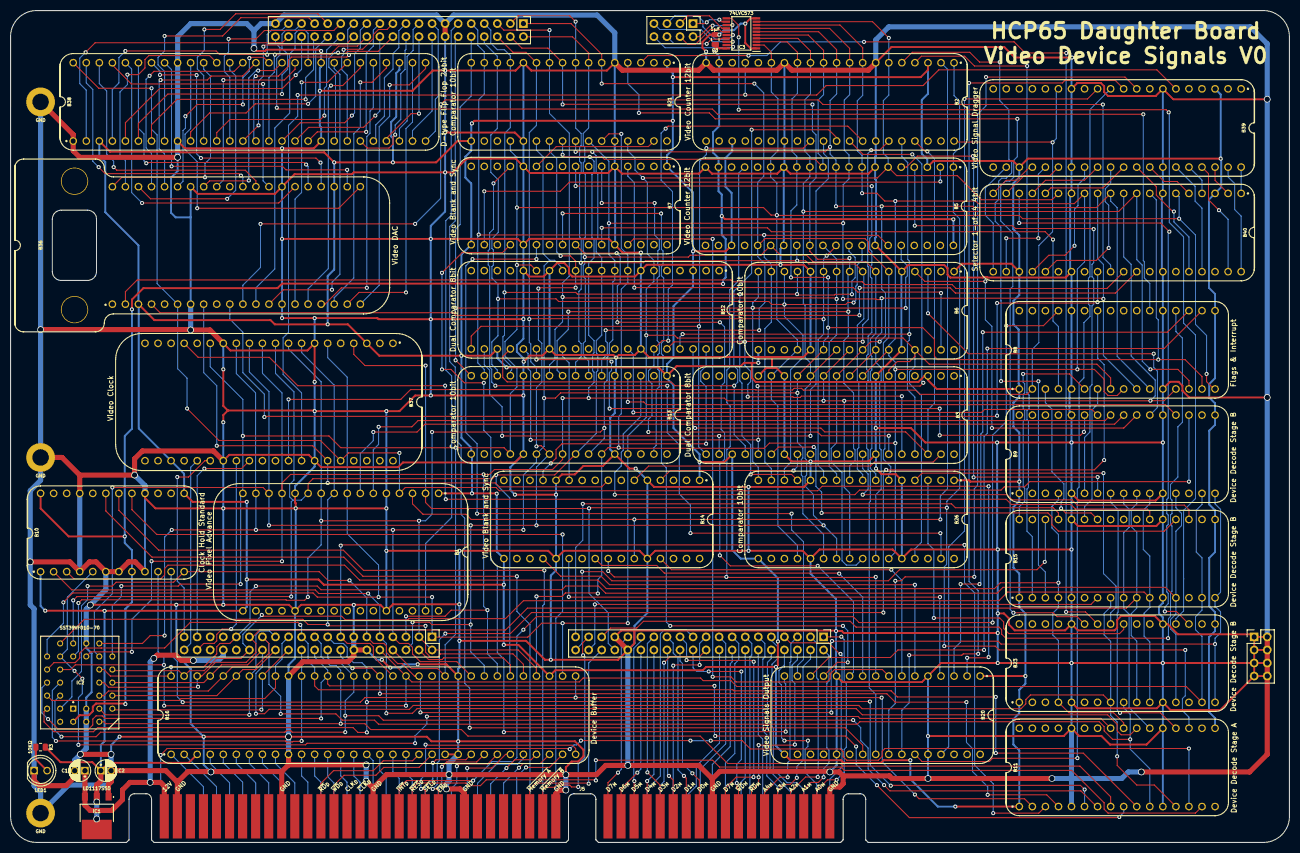
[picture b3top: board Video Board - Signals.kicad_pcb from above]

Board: 2 copper layers, 248.9 x 161.9 mm, 41 parts (0 on the bottom side), 268 nets.
